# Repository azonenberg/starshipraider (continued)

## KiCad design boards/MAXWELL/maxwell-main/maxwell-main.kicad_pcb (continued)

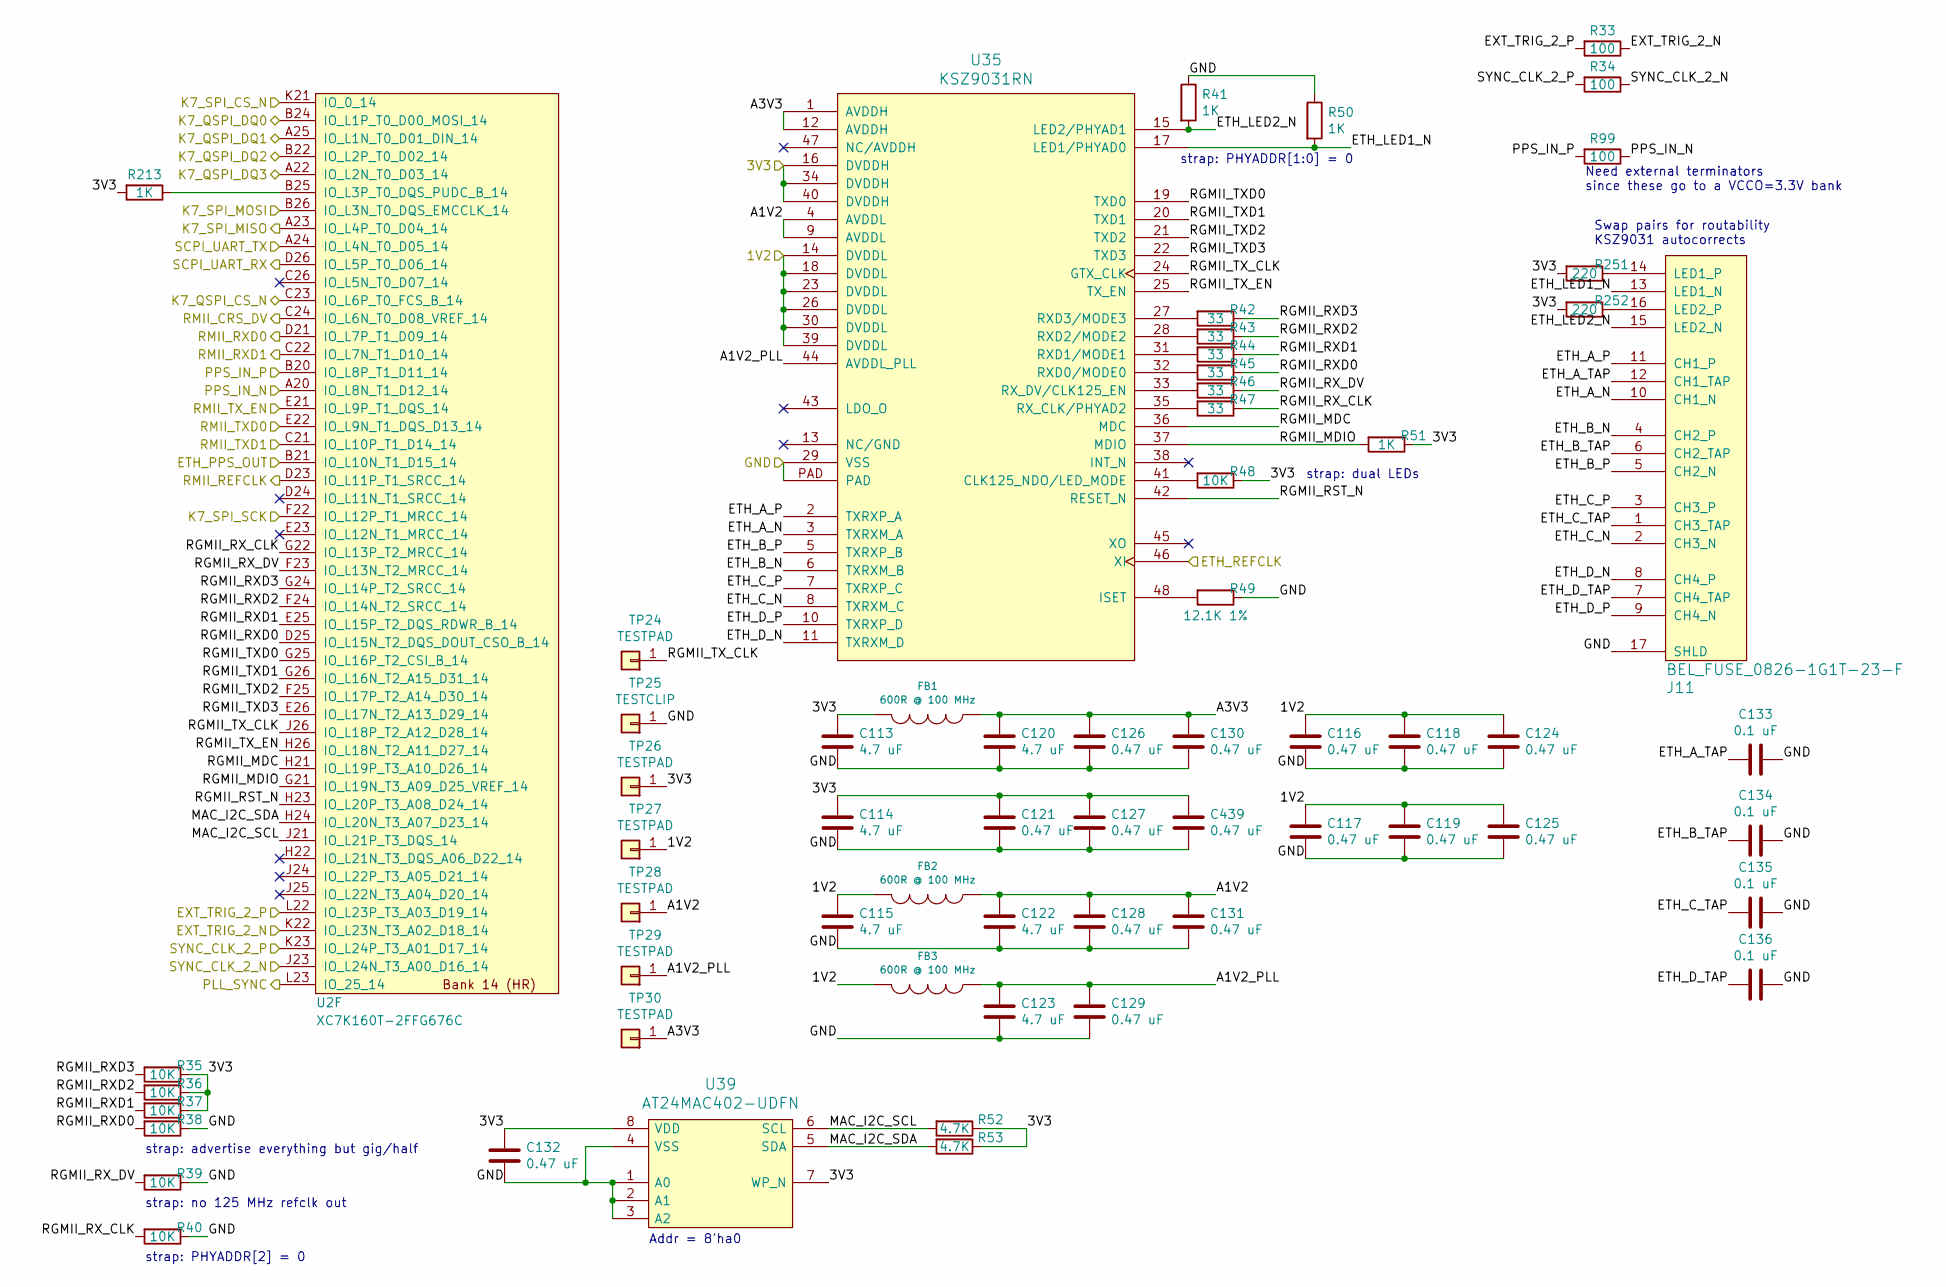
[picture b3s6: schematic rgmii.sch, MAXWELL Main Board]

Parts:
C113, C114, C115, C120, C122, C123: 4.7 uF; EIA_0603_CAP_NOSILK
C116, C117, C118, C119, C121, C124, C125, C126, C127, C128, C129, C130, C131, C132, C439: 0.47 uF; EIA_0402_CAP_NOSILK
C133, C134, C135, C136: 0.1 uF; EIA_0402_CAP_NOSILK
FB1, FB2, FB3: 600R @ 100 MHz; EIA_0603_INDUCTOR_NOSILK
J11: BEL_FUSE_0826-1G1T-23-F; CONN_BELFUSE_0826_1G1T_23_F
R33, R34, R99: 100; EIA_0402_RES_NOSILK
R35, R36, R37, R38, R39, R40, R48: 10K; EIA_0402_RES_NOSILK
R41, R50, R51, R213: 1K; EIA_0402_RES_NOSILK
R42, R43, R44, R45, R46, R47: 33; EIA_0402_RES_NOSILK
R49: 12.1K 1%; EIA_0402_RES_NOSILK
R52, R53: 4.7K; EIA_0402_RES_NOSILK
R251, R252: 220; EIA_0402_RES_NOSILK
TP24, TP26, TP27, TP28, TP29, TP30: TESTPAD; TESTPOINT_SMT_0.5MM
TP25: TESTCLIP; TESTPOINT_SMT_KEYSTONE_5016
U2: XC7K160T-2FFG676C; BGA_676_27x27_FULLARRAY_1MM_FFG676
U35: KSZ9031RN; QFN_48_0.5MM_7x7MM
U39: AT24MAC402-UDFN; DFN_8_0.5MM_2x3MM_TALL

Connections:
/1V2: C115.1, C116.1, C117.1, C118.1, C119.1, C124.1, C125.1, FB2.2, FB3.2, TP27.1, U35.14 (DVDDL), U35.18 (DVDDL), U35.23 (DVDDL), U35.26 (DVDDL), U35.30 (DVDDL), U35.39 (DVDDL); also elsewhere on the board
/3V3: C113.1, C114.1, C121.1, C127.1, C132.1, C439.1, FB1.2, R35.1, R36.1, R37.1, R48.1, R51.1, R52.1, R53.1, R213.2, R251.2, R252.2, TP26.1, U35.16 (DVDDH), U35.34 (DVDDH), U35.40 (DVDDH), U39.7 (WP_N), U39.8 (VDD); also elsewhere on the board
/Clocking/ETH_REFCLK: U35.46 (XI); also elsewhere on the board
/Clocking/EXT_TRIG_2_N: R33.1, U2.K22 (IO_L23N_T3_A02_D18_14); also elsewhere on the board
/Clocking/EXT_TRIG_2_P: R33.2, U2.L22 (IO_L23P_T3_A03_D19_14); also elsewhere on the board
/Clocking/SYNC_CLK_2_N: R34.1, U2.J23 (IO_L24N_T3_A00_D16_14); also elsewhere on the board
/Clocking/SYNC_CLK_2_P: R34.2, U2.K23 (IO_L24P_T3_A01_D17_14); also elsewhere on the board
/GND: C113.2, C114.2, C115.2, C116.2, C117.2, C118.2, C119.2, C120.2, C121.2, C122.2, C123.2, C124.2, C125.2, C126.2, C127.2, C128.2, C129.2, C130.2, C131.2, C132.2, C133.1, C134.1, C135.1, C136.1, C439.2, J11.17 (SHLD), R38.1, R39.1, R40.1, R41.1, R49.1, R50.1, TP25.1, U35.29 (VSS), U35.PAD, U39.1 (A0), U39.2 (A1), U39.3 (A2), U39.4 (VSS); also elsewhere on the board
/K7_QSPI_CS_N: U2.C23 (IO_L6P_T0_FCS_B_14); also elsewhere on the board
/K7_QSPI_DQ0: U2.B24 (IO_L1P_T0_D00_MOSI_14); also elsewhere on the board
/K7_QSPI_DQ1: U2.A25 (IO_L1N_T0_D01_DIN_14); also elsewhere on the board
/K7_QSPI_DQ2: U2.B22 (IO_L2P_T0_D02_14); also elsewhere on the board
/K7_QSPI_DQ3: U2.A22 (IO_L2N_T0_D03_14); also elsewhere on the board
/MCU/ETH_PPS_OUT: U2.B21 (IO_L10N_T1_D15_14); also elsewhere on the board
/MCU/K7_SPI_CS_N: U2.K21 (IO_0_14); also elsewhere on the board
/MCU/K7_SPI_MISO: U2.A23 (IO_L4P_T0_D04_14); also elsewhere on the board
/MCU/K7_SPI_MOSI: U2.B26 (IO_L3N_T0_DQS_EMCCLK_14); also elsewhere on the board
/MCU/K7_SPI_SCK: U2.F22 (IO_L12P_T1_MRCC_14); also elsewhere on the board
/MCU/RMII_CRS_DV: U2.C24 (IO_L6N_T0_D08_VREF_14); also elsewhere on the board
/MCU/RMII_REFCLK: U2.D23 (IO_L11P_T1_SRCC_14); also elsewhere on the board
/MCU/RMII_RXD0: U2.D21 (IO_L7P_T1_D09_14); also elsewhere on the board
/MCU/RMII_RXD1: U2.C22 (IO_L7N_T1_D10_14); also elsewhere on the board
/MCU/RMII_TXD0: U2.E22 (IO_L9N_T1_DQS_D13_14); also elsewhere on the board
/MCU/RMII_TXD1: U2.C21 (IO_L10P_T1_D14_14); also elsewhere on the board
/MCU/RMII_TX_EN: U2.E21 (IO_L9P_T1_DQS_14); also elsewhere on the board
/PLL_SYNC: U2.L23 (IO_25_14); also elsewhere on the board
/PPS_IN_N: R99.1, U2.A20 (IO_L8N_T1_D12_14); also elsewhere on the board
/PPS_IN_P: R99.2, U2.B20 (IO_L8P_T1_D11_14); also elsewhere on the board
/RGMII PHY/A1V2: C122.1, C128.1, C131.1, FB2.1, TP28.1, U35.4 (AVDDL), U35.9 (AVDDL)
/RGMII PHY/A1V2_PLL: C123.1, C129.1, FB3.1, TP29.1, U35.44 (AVDDL_PLL)
/RGMII PHY/A3V3: C120.1, C126.1, C130.1, FB1.1, TP30.1, U35.1 (AVDDH), U35.12 (AVDDH)
/RGMII PHY/ETH_A_N: J11.10 (CH1_N), U35.3 (TXRXM_A)
/RGMII PHY/ETH_A_P: J11.11 (CH1_P), U35.2 (TXRXP_A)
/RGMII PHY/ETH_A_TAP: C133.2, J11.12 (CH1_TAP)
/RGMII PHY/ETH_B_N: J11.4 (CH2_P), U35.6 (TXRXM_B)
/RGMII PHY/ETH_B_P: J11.5 (CH2_N), U35.5 (TXRXP_B)
/RGMII PHY/ETH_B_TAP: C134.2, J11.6 (CH2_TAP)
/RGMII PHY/ETH_C_N: J11.2 (CH3_N), U35.8 (TXRXM_C)
/RGMII PHY/ETH_C_P: J11.3 (CH3_P), U35.7 (TXRXP_C)
/RGMII PHY/ETH_C_TAP: C135.2, J11.1 (CH3_TAP)
/RGMII PHY/ETH_D_N: J11.8 (CH4_P), U35.11 (TXRXM_D)
/RGMII PHY/ETH_D_P: J11.9 (CH4_N), U35.10 (TXRXP_D)
/RGMII PHY/ETH_D_TAP: C136.2, J11.7 (CH4_TAP)
/RGMII PHY/ETH_LED1_N: J11.13 (LED1_N), R50.2, U35.17 (LED1/PHYAD0)
/RGMII PHY/ETH_LED2_N: J11.15 (LED2_N), R41.2, U35.15 (LED2/PHYAD1)
/RGMII PHY/MAC_I2C_SCL: R52.2, U2.J21 (IO_L21P_T3_DQS_14), U39.6 (SCL)
/RGMII PHY/MAC_I2C_SDA: R53.2, U2.H24 (IO_L20N_T3_A07_D23_14), U39.5 (SDA)
/RGMII PHY/RGMII_MDC: U2.H21 (IO_L19P_T3_A10_D26_14), U35.36 (MDC)
/RGMII PHY/RGMII_MDIO: R51.2, U2.G21 (IO_L19N_T3_A09_D25_VREF_14), U35.37 (MDIO)
/RGMII PHY/RGMII_RST_N: U2.H23 (IO_L20P_T3_A08_D24_14), U35.42 (RESET_N)
/RGMII PHY/RGMII_RXD0: R38.2, R45.1, U2.D25 (IO_L15N_T2_DQS_DOUT_CSO_B_14)
/RGMII PHY/RGMII_RXD1: R37.2, R44.1, U2.E25 (IO_L15P_T2_DQS_RDWR_B_14)
/RGMII PHY/RGMII_RXD2: R36.2, R43.1, U2.F24 (IO_L14N_T2_SRCC_14)
/RGMII PHY/RGMII_RXD3: R35.2, R42.1, U2.G24 (IO_L14P_T2_SRCC_14)
/RGMII PHY/RGMII_RX_CLK: R40.2, R47.1, U2.G22 (IO_L13P_T2_MRCC_14)
/RGMII PHY/RGMII_RX_DV: R39.2, R46.1, U2.F23 (IO_L13N_T2_MRCC_14)
/RGMII PHY/RGMII_TXD0: U2.G25 (IO_L16P_T2_CSI_B_14), U35.19 (TXD0)
/RGMII PHY/RGMII_TXD1: U2.G26 (IO_L16N_T2_A15_D31_14), U35.20 (TXD1)
/RGMII PHY/RGMII_TXD2: U2.F25 (IO_L17P_T2_A14_D30_14), U35.21 (TXD2)
/RGMII PHY/RGMII_TXD3: U2.E26 (IO_L17N_T2_A13_D29_14), U35.22 (TXD3)
/RGMII PHY/RGMII_TX_CLK: TP24.1, U2.J26 (IO_L18P_T2_A12_D28_14), U35.24 (GTX_CLK)
/RGMII PHY/RGMII_TX_EN: U2.H26 (IO_L18N_T2_A11_D27_14), U35.25 (TX_EN)
/SCPI_UART_RX: U2.D26 (IO_L5P_T0_D06_14); also elsewhere on the board
/SCPI_UART_TX: U2.A24 (IO_L4N_T0_D05_14); also elsewhere on the board
unnamed: J11.14 (LED1_P), R251.1
unnamed: J11.16 (LED2_P), R252.1
unnamed: R42.2, U35.27 (RXD3/MODE3)
unnamed: R43.2, U35.28 (RXD2/MODE2)
unnamed: R44.2, U35.31 (RXD1/MODE1)
unnamed: R45.2, U35.32 (RXD0/MODE0)
unnamed: R46.2, U35.33 (RX_DV/CLK125_EN)
unnamed: R47.2, U35.35 (RX_CLK/PHYAD2)
unnamed: R48.2, U35.41 (CLK125_NDO/LED_MODE)
unnamed: R49.2, U35.48 (ISET)
unnamed: R213.1, U2.B25 (IO_L3P_T0_DQS_PUDC_B_14)

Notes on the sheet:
Need external terminators since these go to a VCCO=3.3V bank
strap: PHYADDR[1:0] = 0
strap: dual LEDs
strap: advertise everything but gig/half
strap: no 125 MHz refclk out
strap: PHYADDR[2] = 0
Addr = 8'ha0
Swap pairs for routability KSZ9031 autocorrects

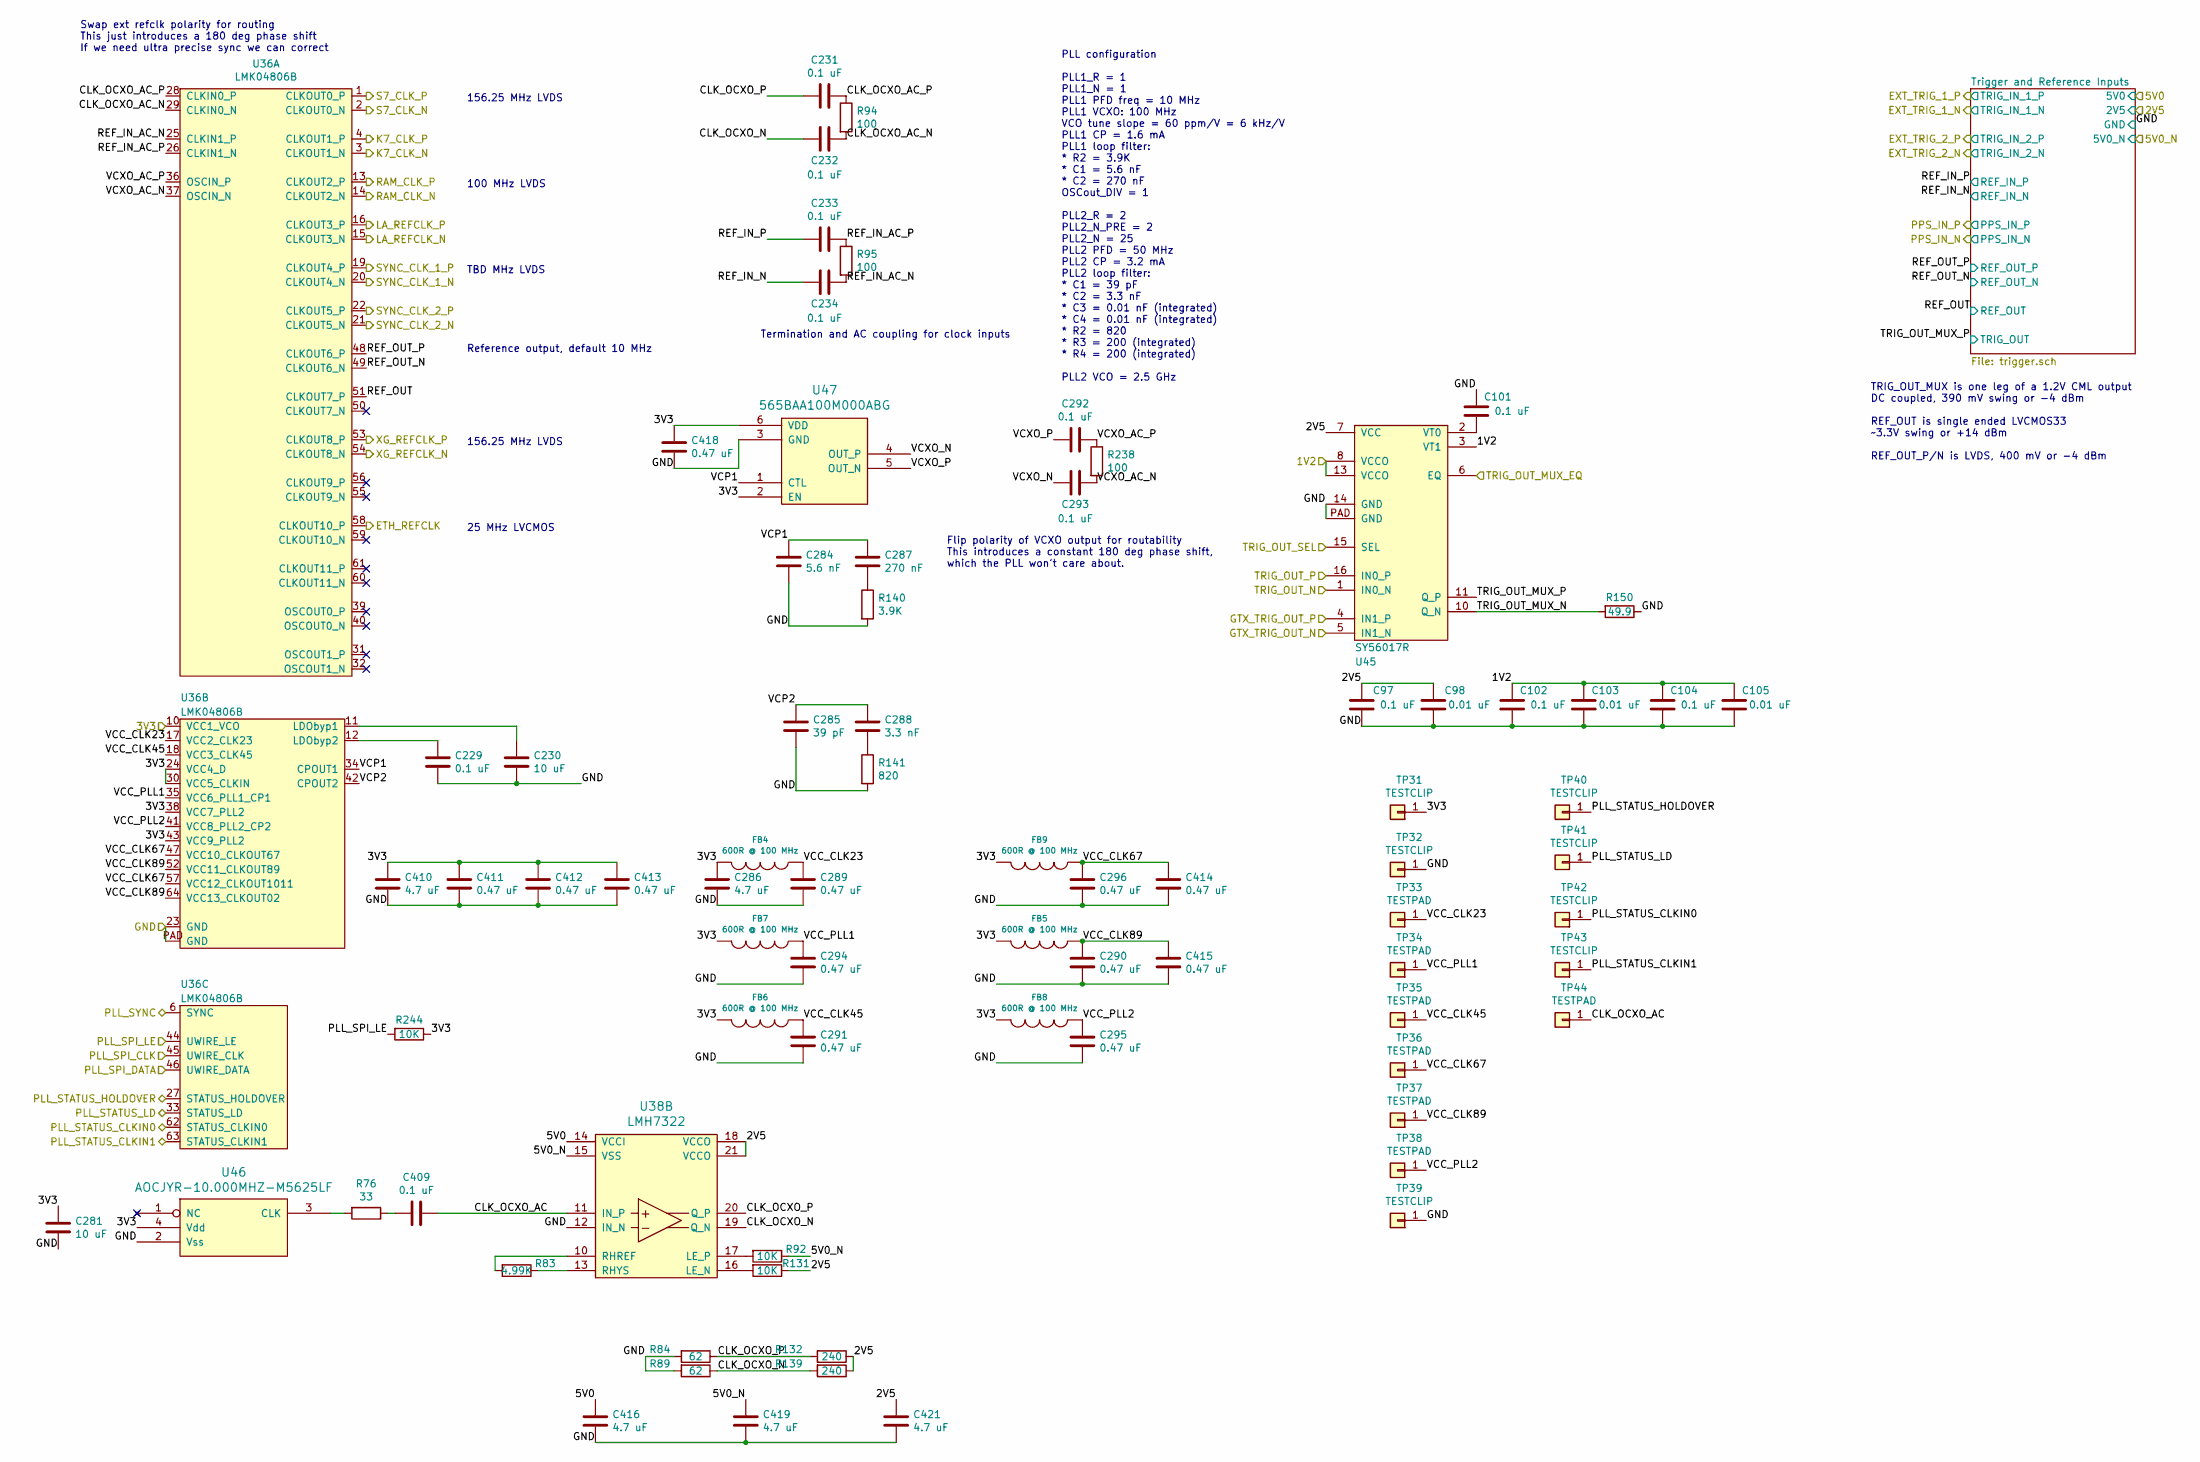
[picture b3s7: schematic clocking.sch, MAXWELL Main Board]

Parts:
C97, C101, C102, C104, C229, C231, C232, C233, C234, C292, C293, C409: 0.1 uF; EIA_0402_CAP_NOSILK
C98, C103, C105: 0.01 uF; EIA_0402_CAP_NOSILK
C230: 10 uF; EIA_0805_CAP_NOSILK
C281: 10 uF; EIA_1206_CAP_NOSILK
C284: 5.6 nF; EIA_0402_CAP_NOSILK
C285: 39 pF; EIA_0402_CAP_NOSILK
C286, C410, C416, C419, C421: 4.7 uF; EIA_0603_CAP_NOSILK
C287: 270 nF; EIA_0603_CAP_NOSILK
C288: 3.3 nF; EIA_0603_CAP_NOSILK
C289, C290, C291, C294, C295, C296, C411, C412, C413, C414, C415, C418: 0.47 uF; EIA_0402_CAP_NOSILK
FB4, FB5, FB6, FB7, FB8, FB9: 600R @ 100 MHz; EIA_0603_INDUCTOR_NOSILK
R76: 33; EIA_0402_RES_NOSILK
R83: 4.99K; EIA_0402_RES_NOSILK
R84, R89: 62; EIA_0402_RES_NOSILK
R92, R131, R244: 10K; EIA_0402_RES_NOSILK
R94, R95, R238: 100; EIA_0402_RES_NOSILK
R132, R139: 240; EIA_0402_RES_NOSILK
R140: 3.9K; EIA_0402_RES_NOSILK
R141: 820; EIA_0402_RES_NOSILK
R150: 49.9; EIA_0402_RES_NOSILK
TP31, TP32, TP39, TP40, TP41, TP42, TP43: TESTCLIP; TESTPOINT_SMT_KEYSTONE_5016
TP33, TP34, TP35, TP36, TP37, TP38, TP44: TESTPAD; TESTPOINT_SMT_0.5MM
U36: LMK04806B; QFN_64_0.5MM_9x9MM
U38: LMH7322; QFN_24_0.5MM_4x4MM
U45: SY56017R; QFN_16_0.5MM_3x3MM
U46: AOCJYR-10.000MHZ-M5625LF; OSC_ABRACON_AOCJYR
U47: 565BAA100M000ABG; OSCILLATOR_LVDS_7.0x5.0

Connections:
/1V2: C102.1, C103.1, C104.1, C105.1, U45.3 (VT1), U45.8 (VCCO), U45.13 (VCCO); also elsewhere on the board
/2V5: C97.1, C98.1, C421.1, R131.1, R132.1, R139.1, U38.18 (VCCO), U38.21 (VCCO), U45.7 (VCC); also elsewhere on the board
/3V3: C281.1, C286.1, C410.1, C411.1, C412.1, C413.1, C418.1, FB4.2, FB5.2, FB6.2, FB7.2, FB8.2, FB9.2, R244.1, TP31.1, U36.10 (VCC1_VCO), U36.24 (VCC4_D), U36.30 (VCC5_CLKIN), U36.38 (VCC7_PLL2), U36.43 (VCC9_PLL2), U46.4 (Vdd), U47.2 (EN), U47.6 (VDD); also elsewhere on the board
/5V0: C416.1, U38.14 (VCCI); also elsewhere on the board
/5V0_N: C419.1, R92.1, U38.15 (VSS); also elsewhere on the board
/Clocking/CLK_OCXO_AC: C409.1, TP44.1, U38.11 (IN_P)
/Clocking/CLK_OCXO_AC_N: C232.1, R94.2, U36.29 (CLKIN0_N)
/Clocking/CLK_OCXO_AC_P: C231.1, R94.1, U36.28 (CLKIN0_P)
/Clocking/CLK_OCXO_N: C232.2, R89.1, R139.2, U38.19 (Q_N)
/Clocking/CLK_OCXO_P: C231.2, R84.1, R132.2, U38.20 (Q_P)
/Clocking/ETH_REFCLK: U36.58 (CLKOUT10_P); also elsewhere on the board
/Clocking/GTX_TRIG_OUT_N: U45.5 (IN1_N); also elsewhere on the board
/Clocking/GTX_TRIG_OUT_P: U45.4 (IN1_P); also elsewhere on the board
/Clocking/K7_CLK_N: U36.3 (CLKOUT1_N); also elsewhere on the board
/Clocking/K7_CLK_P: U36.4 (CLKOUT1_P); also elsewhere on the board
/Clocking/LA_REFCLK_N: U36.15 (CLKOUT3_N); also elsewhere on the board
/Clocking/LA_REFCLK_P: U36.16 (CLKOUT3_P); also elsewhere on the board
/Clocking/RAM_CLK_N: U36.14 (CLKOUT2_N); also elsewhere on the board
/Clocking/RAM_CLK_P: U36.13 (CLKOUT2_P); also elsewhere on the board
/Clocking/REF_IN_AC_N: C234.1, R95.2, U36.25 (CLKIN1_P)
/Clocking/REF_IN_AC_P: C233.1, R95.1, U36.26 (CLKIN1_N)
/Clocking/REF_IN_N: C234.2; also elsewhere on the board
/Clocking/REF_IN_P: C233.2; also elsewhere on the board
/Clocking/REF_OUT: U36.51 (CLKOUT7_P); also elsewhere on the board
/Clocking/REF_OUT_N: U36.49 (CLKOUT6_N); also elsewhere on the board
/Clocking/REF_OUT_P: U36.48 (CLKOUT6_P); also elsewhere on the board
/Clocking/S7_CLK_N: U36.2 (CLKOUT0_N); also elsewhere on the board
/Clocking/S7_CLK_P: U36.1 (CLKOUT0_P); also elsewhere on the board
/Clocking/SYNC_CLK_1_N: U36.20 (CLKOUT4_N); also elsewhere on the board
/Clocking/SYNC_CLK_1_P: U36.19 (CLKOUT4_P); also elsewhere on the board
/Clocking/SYNC_CLK_2_N: U36.21 (CLKOUT5_N); also elsewhere on the board
/Clocking/SYNC_CLK_2_P: U36.22 (CLKOUT5_P); also elsewhere on the board
/Clocking/TRIG_OUT_MUX_N: R150.2, U45.10 (Q_N)
/Clocking/TRIG_OUT_MUX_P: U45.11 (Q_P); also elsewhere on the board
/Clocking/TRIG_OUT_N: U45.1 (IN0_N); also elsewhere on the board
/Clocking/TRIG_OUT_P: U45.16 (IN0_P); also elsewhere on the board
/Clocking/VCC_CLK23: C289.1, FB4.1, TP33.1, U36.17 (VCC2_CLK23)
/Clocking/VCC_CLK45: C291.1, FB6.1, TP35.1, U36.18 (VCC3_CLK45)
/Clocking/VCC_CLK67: C296.1, C414.1, FB9.1, TP36.1, U36.47 (VCC10_CLKOUT67), U36.57 (VCC12_CLKOUT1011)
/Clocking/VCC_CLK89: C290.1, C415.1, FB5.1, TP37.1, U36.52 (VCC11_CLKOUT89), U36.64 (VCC13_CLKOUT02)
/Clocking/VCC_PLL1: C294.1, FB7.1, TP34.1, U36.35 (VCC6_PLL1_CP1)
/Clocking/VCC_PLL2: C295.1, FB8.1, TP38.1, U36.41 (VCC8_PLL2_CP2)
/Clocking/VCP1: C284.1, C287.1, U36.34 (CPOUT1), U47.1 (CTL)
/Clocking/VCP2: C285.1, C288.1, U36.42 (CPOUT2)
/Clocking/VCXO_AC_N: C293.1, R238.2, U36.37 (OSCIN_N)
/Clocking/VCXO_AC_P: C292.1, R238.1, U36.36 (OSCIN_P)
/Clocking/VCXO_N: C293.2, U47.4 (OUT_P)
/Clocking/VCXO_P: C292.2, U47.5 (OUT_N)
/Clocking/XG_REFCLK_N: U36.54 (CLKOUT8_N); also elsewhere on the board
/Clocking/XG_REFCLK_P: U36.53 (CLKOUT8_P); also elsewhere on the board
/GND: C97.2, C98.2, C101.1, C102.2, C103.2, C104.2, C105.2, C229.2, C230.2, C281.2, C284.2, C285.2, C286.2, C289.2, C290.2, C291.2, C294.2, C295.2, C296.2, C410.2, C411.2, C412.2, C413.2, C414.2, C415.2, C416.2, C418.2, C419.2, C421.2, R84.2, R89.2, R140.2, R141.2, R150.1, TP32.1, TP39.1, U36.23 (GND), U36.PAD (GND), U38.12 (IN_N), U45.14 (GND), U45.PAD (GND), U46.2 (Vss), U47.3 (GND); also elsewhere on the board
/PLL_SPI_CLK: U36.45 (UWIRE_CLK); also elsewhere on the board
/PLL_SPI_DATA: U36.46 (UWIRE_DATA); also elsewhere on the board
/PLL_SPI_LE: R244.2, U36.44 (UWIRE_LE); also elsewhere on the board
/PLL_STATUS_CLKIN0: TP42.1, U36.62 (STATUS_CLKIN0); also elsewhere on the board
/PLL_STATUS_CLKIN1: TP43.1, U36.63 (STATUS_CLKIN1); also elsewhere on the board
/PLL_STATUS_HOLDOVER: TP40.1, U36.27 (STATUS_HOLDOVER); also elsewhere on the board
/PLL_STATUS_LD: TP41.1, U36.33 (STATUS_LD); also elsewhere on the board
/PLL_SYNC: U36.6 (SYNC); also elsewhere on the board
/TRIG_OUT_MUX_EQ: U45.6 (EQ); also elsewhere on the board
/TRIG_OUT_SEL: U45.15 (SEL); also elsewhere on the board
unnamed: C101.2, U45.2 (VT0)
unnamed: C229.1, U36.12 (LDObyp2)
unnamed: C230.1, U36.11 (LDObyp1)
unnamed: C287.2, R140.1
unnamed: C288.2, R141.1
unnamed: C409.2, R76.1
unnamed: R76.2, U46.3 (CLK)
unnamed: R83.1, U38.13 (RHYS)
unnamed: R83.2, U38.10 (RHREF)
unnamed: R92.2, U38.17 (LE_P)
unnamed: R131.2, U38.16 (LE_N)

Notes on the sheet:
25 MHz LVCMOS
156.25 MHz LVDS
100 MHz LVDS
TBD MHz LVDS
Reference output, default 10 MHz
Termination and AC coupling for clock inputs
PLL configuration PLL1_R = 1 PLL1_N = 1 PLL1 PFD freq = 10 MHz PLL1 VCXO: 100 MHz VCO tune slope = 60 ppm/V = 6 kHz/V PLL1 CP = 1.6 mA PLL1 loop filter: * R2 = 3.9K * C1 = 5.6 nF * C2 = 270 nF OSCout_DIV = 1 PLL2_R = 2 PLL2_N_PRE = 2 PLL2_N = 25 PLL2 PFD = 50 MHz PLL2 CP = 3.2 mA PLL2 loop filter: 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
TRIG_OUT_MUX is one leg of a 1.2V CML output DC coupled, 390 mV swing or -4 dBm REF_OUT is single ended LVCMOS33 ~~3.3V swing or +14 dBm REF_OUT_P/N is LVDS, 400 mV or -4 dBm
Swap ext refclk polarity for routing This just introduces a 180 deg phase shift If we need ultra precise sync we can correct
Flip polarity of VCXO output for routability This introduces a constant 180 deg phase shift, which the PLL won't care about.
